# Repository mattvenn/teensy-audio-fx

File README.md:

# Teensy FX

* A [Teensy 4](https://www.pjrc.com/teensy-4-0/) based FX unit with [Pocket Operator](https://teenage.engineering/products/po) style and playability.
* 12 knobs, 4 buttons each with LED, and 4 LEDs showing automation cycle.
* Combination of filtered reverb, ping pong filtered delay and a noise source, but this is [customisable](#Audio-patch).
* Each knob can be automated (a bit like punch in effects on the Pocket Operators)
* Tap tempo and PO sync
* [video series on development and use of the teensy-fx](https://www.youtube.com/playlist?list=PLmcDgdDpcaPg4DthWWuq7HqhB-hiN_gUg)

# Hardware

[schematic](hardware/schematic.pdf)

[gerbers](hardware/teensy-fx-2020-02-10-fab.zip)

[photos](https://photos.app.goo.gl/ELiSmwA5KhBPN7PL9)

[noise performance](docs/noise.md)

Buy the right parts through the links on the [kitspace page](https://kitspace.org/boards/github.com/mattvenn/teensy-audio-fx).

## Hardware Resources

Based off the teensy 4 audio board and the [teensy beats shield](https://hackaday.io/project/161127-teensy-beats-shield)

* teensy 4 audio board schematic https://www.pjrc.com/store/schematic_audio4.png
* [SGTL5000 datasheet](https://static6.arrow.com/aropdfconversion/d5e3ddfdb01ac7d0ee29dd23626c23e0eb18a14a/1931605559406471sgtl5000.pdf)
* TLC5947 24 channel PWM LED driver
* 4067 multiplexer for the knobs
* pot RK09K1130AP5

## Hardware V1: git commit 99c1038

check the git repo out to the [hash](https://github.com/mattvenn/teensy-audio-fx/tree/99c1038) to make sure everything is in sync.

### Errata

* Do not place C16
* Swap LRCLK & BCLK - see pic [lrclk-bclk-swap](docs/lrclk-bclk-swap.png)
* 2.2uF ceramics sound as good and are much cheaper than the 1uF acrylics for C8, C9, C14 & C15

## Hardware V2: git master

* test points for mic input
* separate regulator for pot 3.3v to reduce noise?
* put leds and buttons below pots for easier viewing and pressing
* leave space on back for rubber feet
* update FP of audio sockets to new FP - audio sockets weren't available in EU, changed to 35RASMT2BHNTRX which has 5 pads but will fit on the same fp
* filter behind pot mux was a mistake. filters must be in front of mux or removed - fixed by removing
* fix LRCLK & BCLK mixup - fixed

## Back graphic

* Art by Kipling: http://bit.ly/39Wxc4R. Designed in ContextFree
* 100 x 60mm == 3.94 x 2.36" == 1182 x 708 pix

# FW

* each knob controls one of the parameters
* each knob has a number of steps of recordable automation
* knob's leds brightness shows current value of parameter
* record time is based on bpm tap tempo and number of steps (4 bars in control.py)
* buttons are: tap tempo/sync, write, erase and start automation loop from beginning
* press & hold tempo button to switch between tap tempo and [PO sync mode](docs/PO_sync_mode.md)
* press write and move a knob to record its movement
* moving a knob without pressing record will wipe the pattern and set it all to the current knob value
* 4 leds on top right show progression through the automation loop

## Uploading

* remove modemmanager
* install teensy rules: https://www.pjrc.com/teensy/00-teensy.rules

    sudo cp 49-teensy.rules /etc/udev/rules.d
    sudo udevadm control --reload-rules
    sudo udevadm trigger

Then:

    make prog

## issues

* freeverb [noise issue](https://forum.pjrc.com/threads/57046-Freeverb-with-low-input-levels-gt-noise-and-wierd-oscillating-quot-tone-quot) fixed [here](https://github.com/PaulStoffregen/Audio/pull/357)
    * to fix this you can copy the local effect_freeverb over the one in ~/.platformio
* if delay is not as long as expected (should be seconds), check teensy audio lib is up to date, older versions [didn't support teensy4's large memory](https://github.com/PaulStoffregen/Audio/commit/bbcfe3bd201d86aa7aa0e87d97c989f4259465de)

# Audio patch

made with https://www.pjrc.com/teensy/gui/index.html

# Software

[control.py](control.py) is a PyQT program that was developed in order to make an MVP
interface that could later be translated to hardware in the form of a PCB.

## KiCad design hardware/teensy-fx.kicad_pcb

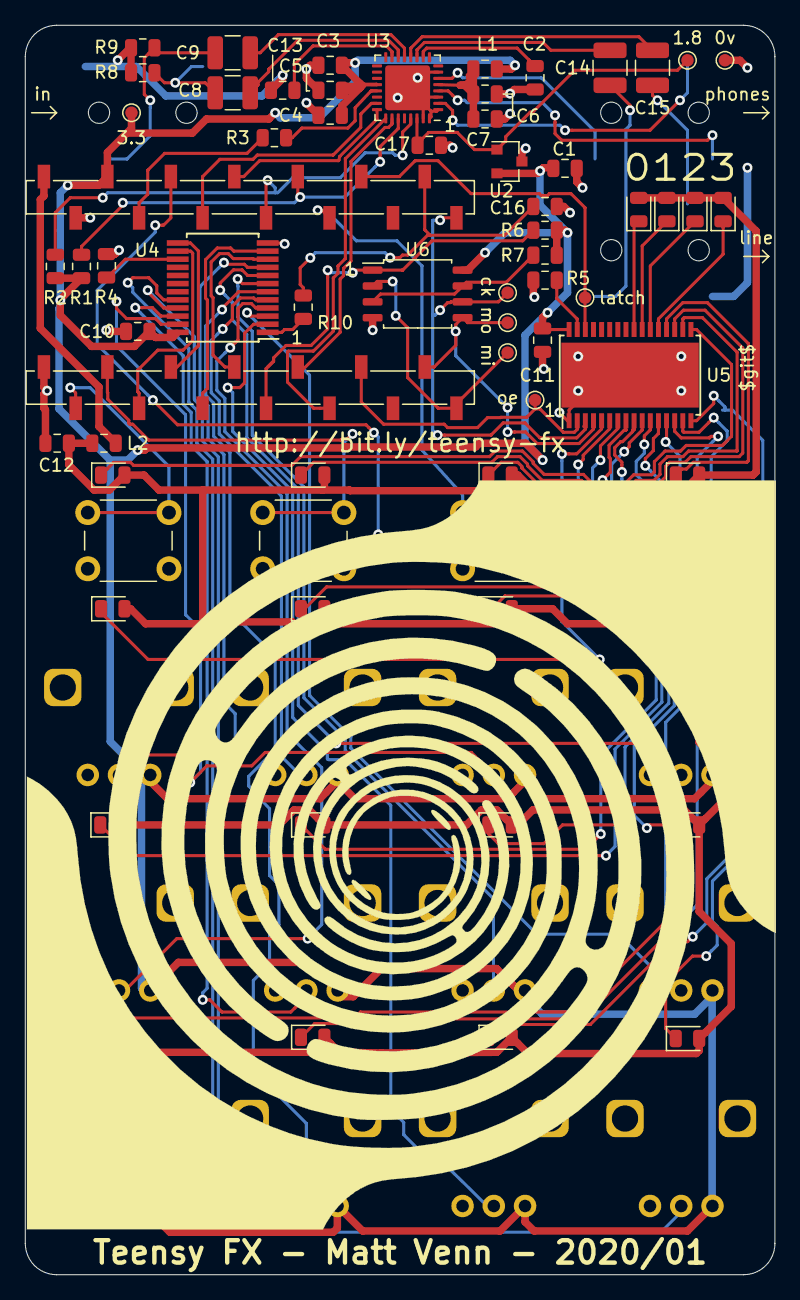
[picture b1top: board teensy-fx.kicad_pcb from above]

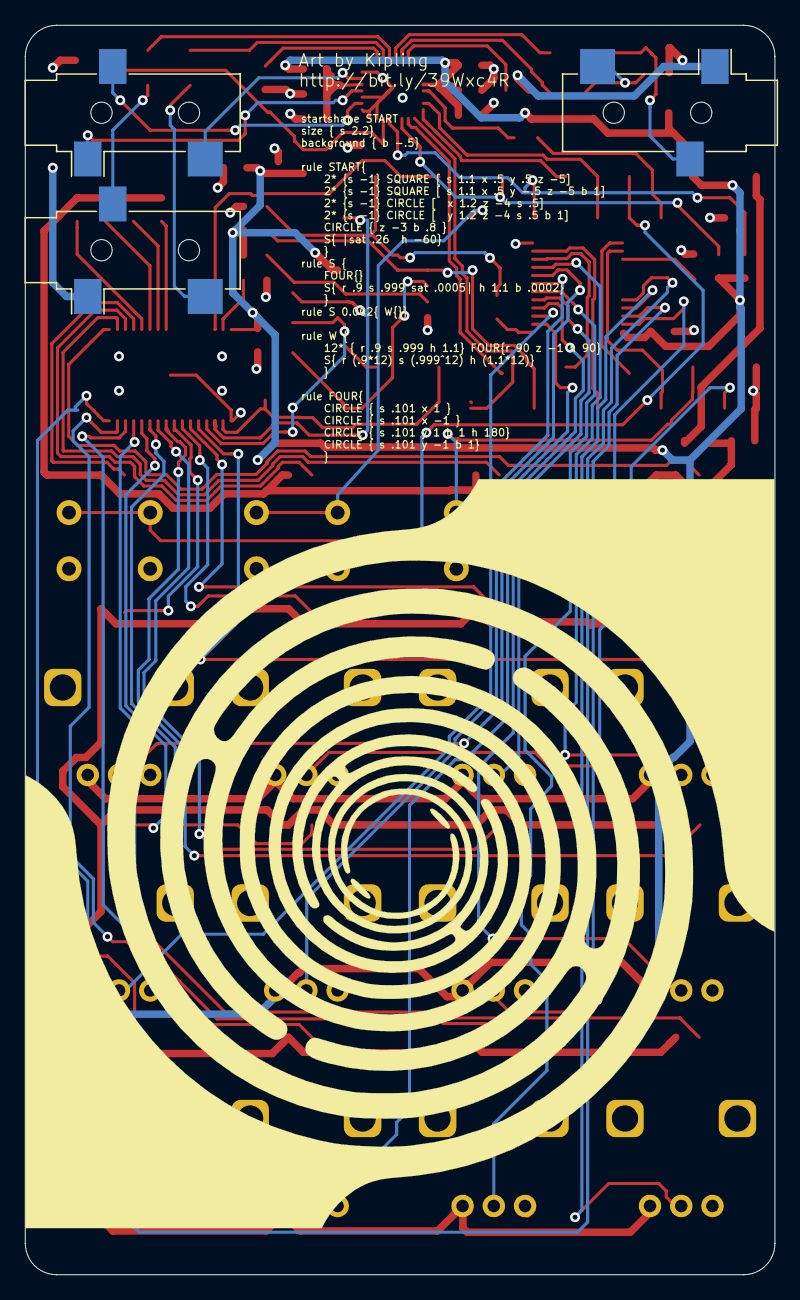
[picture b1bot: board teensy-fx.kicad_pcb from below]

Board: 4 copper layers, 60.0 x 100.0 mm, 82 parts (3 on the bottom side), 78 nets.

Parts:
C1, C3, C6, C10, C11, C12, C16, C17: 2.2uF; C_0805_2012Metric
C2, C4, C5, C7, C13: 0.1uF; C_0805_2012Metric
C8, C9, C14, C15: 1uF; C_1210_3225Metric
D1, D2, D3, D4, D5, D6, D7, D8, D9, D10, D11, D12, D13, D14, D15, D16, D17, D18, D19, D20: LED; LED_0805_2012Metric
J1, J2, J3: AudioJack3_Ground; Jack_3.5mm_CUI_SJ-3523-SMT_Horizontal
L1, L2: 600R; L_0805_2012Metric
R1, R2: 2.2K; R_0805_2012Metric
R3, R10: 100R; R_0805_2012Metric
R4, R6, R7: 10k; R_0805_2012Metric
R5: 4.7k; R_0805_2012Metric
R8, R9: 100k; R_0805_2012Metric
RV1, RV2, RV3, RV4, RV5, RV6, RV7, RV8, RV9, RV10, RV11, RV12: R_POT; Potentiometer_Alps_RK09L_Single_Vertical
SW1, SW2, SW3, SW4: Switch_SW_Push; SW_PUSH_6mm
TP1, TP2, TP3, TP4, TP5, TP6, TP7, TP8: TestPoint; TestPoint_Pad_D1.0mm
U1: Teensy4.0; teensy4smt
U2: MCP1811A; SOT-23
U3: SGTL5000; QFN-32-1EP_5x5mm_P0.5mm_EP3.6x3.6mm
U4: 4067; SSOP-24_5.3x8.2mm_P0.65mm
U5: TLC5947DAP; HTSSOP-32-1EP_6.1x11mm_P0.65mm_EP5.2x11mm_Mask4.11x4.36mm
U6: W25Q128JVS; SOIC-8_5.23x5.23mm_P1.27mm

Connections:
+1V8: C17.1, TP7.1, U2.1, U3.30
+3V3: C1.1, C3.1, C4.1, C5.1, C10.1, C11.1, L1.1, R1.1, R2.1, R6.1, R7.1, RV1.1, RV2.1, RV3.1, RV4.1, RV5.1, RV6.1, RV7.1, RV8.1, RV9.1, RV10.1, RV11.1, RV12.1, TP6.1, U1.31, U2.2, U3.20, U4.24, U5.32, U6.8
+5V: L2.1, U1.33
+5VA: C12.1, D1.2, D2.2, D3.2, D4.2, D5.2, D6.2, D7.2, D8.2, D9.2, D10.2, D11.2, D12.2, D13.2, D14.2, D15.2, D16.2, D17.2, D18.2, D19.2, D20.2, L2.2
/SGTL audio/filter_audio_3v3: C6.1, C7.1, L1.2, U3.5
/mem_cs: R6.2, U1.8, U6.1
/pots buttons & LEDs/a0: RV1.2, U4.9
/pots buttons & LEDs/a1: RV4.2, U4.8
/pots buttons & LEDs/a2: RV7.2, U4.7
/pots buttons & LEDs/a3: RV10.2, U4.6
/pots buttons & LEDs/a4: RV2.2, U4.5
/pots buttons & LEDs/a5: RV5.2, U4.4
/pots buttons & LEDs/a6: RV8.2, U4.3
/pots buttons & LEDs/a7: RV11.2, U4.2
/pots buttons & LEDs/a8: RV3.2, U4.23
/pots buttons & LEDs/a9: RV6.2, U4.22
/pots buttons & LEDs/a10: RV9.2, U4.21
/pots buttons & LEDs/a11: RV12.2, U4.20
BCLK: U1.28, U3.23
GND: C1.2, C2.2, C3.2, C4.2, C5.2, C6.2, C7.2, C10.2, C11.2, C12.2, C13.2, C16.2, C17.2, J1.S, J3.S, R4.2, R5.2, R8.2, R9.1, RV1.3, RV2.3, RV3.3, RV4.3, RV5.3, RV6.3, RV7.3, RV8.3, RV9.3, RV10.3, RV11.3, RV12.3, SW1.2, SW2.2, SW3.2, SW4.2, TP8.1, U1.1, U1.32, U2.3, U3.1, U3.3, U3.7, U3.31, U3.32, U3.33, U4.12, U5.1, U5.33, U6.4
I2S_IN: U1.10, U3.25
I2S_OUT: U1.9, U3.26
LRCLK: U1.27, U3.24
MCLK: R3.2, U1.30
MISO: TP5.1, U1.14, U6.2
MOSI: TP3.1, U1.13, U5.4, U6.5
unnamed: C2.1, U3.10
unnamed: C8.1, U3.14
unnamed: C8.2, J1.T, R8.1
unnamed: C9.1, U3.13
unnamed: C9.2, J1.R, R9.2
unnamed: C13.1, U3.15
unnamed: C14.1, U3.11
unnamed: C14.2, J3.T
unnamed: C15.1, U3.12
unnamed: C15.2, J3.R
unnamed: D1.1, U5.5
unnamed: D2.1, U5.6
unnamed: D3.1, U5.7
unnamed: D4.1, U5.8
unnamed: D5.1, U5.9
unnamed: D6.1, U5.10
unnamed: D7.1, U5.11
unnamed: D8.1, U5.12
unnamed: D9.1, U5.13
unnamed: D10.1, U5.14
unnamed: D11.1, U5.15
unnamed: D12.1, U5.16
unnamed: D13.1, U5.17
unnamed: D14.1, U5.18
unnamed: D15.1, U5.19
unnamed: D16.1, U5.20
unnamed: D17.1, U5.21
unnamed: D18.1, U5.22
unnamed: D19.1, U5.23
unnamed: D20.1, U5.24
unnamed: J2.R, U3.2
unnamed: J2.S, U3.4
unnamed: J2.T, U3.6
unnamed: R3.1, U3.21
unnamed: R4.1, U4.15
unnamed: R5.1, U5.31
unnamed: R7.2, U6.3, U6.7
unnamed: R10.1, U4.1
SCL: R2.2, U1.26, U3.29
SCLK: TP1.1, U1.20, U5.3, U6.6
SDA: R1.2, U1.25, U3.27
led_latch: TP4.1, U1.23, U5.30
led_oe: TP2.1, U1.11, U5.2
pot_b0: U1.7, U4.10
pot_b1: U1.6, U4.11
pot_b2: U1.4, U4.14
pot_b3: U1.5, U4.13
pot_multiplex: C16.1, R10.2, U1.21
sw_1: SW1.1, U1.2
sw_2: SW2.1, U1.3
sw_3: SW3.1, U1.24
sw_4: SW4.1, U1.29

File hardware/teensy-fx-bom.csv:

"Ref","Qnty","Value","Cmp name","Footprint","Description","Vendor","Vendor P/N","farnell #","MOQ","Lead Time"
"C1, C3, C6, C10, C11, C12, C16, C17, ","8","2.2uF","C_Small","Capacitor_SMD:C_0805_2012Metric","Unpolarized capacitor, small symbol","","","2773238","",""
"C2, C4, C5, C7, C13, ","5","0.1uF","C_Small","Capacitor_SMD:C_0805_2012Metric","Unpolarized capacitor, small symbol","","","1414663","",""
"C8, C9, C14, C15, ","4","1uF","C_Small","Capacitor_SMD:C_1210_3225Metric","Unpolarized capacitor, small symbol","","","2112915","",""
"D1, D2, D3, D4, D5, D6, D7, D8, D9, D10, D11, D12, D13, D14, D15, D16, D17, D18, D19, D20, ","20","LED","LED","LED_SMD:LED_0805_2012Metric","Light emitting diode","","","2099236","",""
"J1, J2, J3, ","3","AudioJack3_Ground","AudioJack3","audio-fx:Jack_3.5mm_CUI_SJ-3523-SMT_Horizontal","Audio Jack, 3 Poles (Stereo / TRS)","","","2915138","",""
"L1, L2, ","2","600R","Ferrite_Bead_Small","Inductor_SMD:L_0805_2012Metric","Ferrite bead, small symbol","","","2215655","",""
"R1, R2, ","2","2.2K","R","Resistor_SMD:R_0805_2012Metric","Resistor","","","1469887","",""
"R3, R10, ","2","100R","R","Resistor_SMD:R_0805_2012Metric","Resistor","","","1469862","",""
"R4, R6, R7, ","3","10k","R","Resistor_SMD:R_0805_2012Metric","Resistor","","","2906645","",""
"R5, ","1","4.7k","R","Resistor_SMD:R_0805_2012Metric","Resistor","","","1469923","",""
"R8, R9, ","2","100k","R","Resistor_SMD:R_0805_2012Metric","Resistor","","","1469860","",""
"RV1, RV2, RV3, RV4, RV5, RV6, RV7, RV8, RV9, RV10, RV11, RV12, ","12","R_POT","R_POT","audio-fx:Potentiometer_Alps_RK09L_Single_Vertical","Potentiometer","","","","",""
"SW1, SW2, SW3, SW4, ","4","Switch_SW_Push","Switch_SW_Push-teensy_beats-cache","Button_Switch_THT:SW_PUSH_6mm","","","","dnp","",""
"TP1, TP2, TP3, TP4, TP5, TP6, TP7, TP8, ","8","TestPoint","TestPoint","TestPoint:TestPoint_Pad_D1.0mm","test point","","","dnp","",""
"U1, ","1","Teensy4.0","Teensy4.0","audio-fx:teensy4smt","","","","2847911","",""
"U2, ","1","MCP1811A","ldo","Package_TO_SOT_SMD:SOT-23","","","","2990195","",""
"U3, ","1","SGTL5000","SparkFun-IC-Analog_SGTL5000-teensy_beats-cache","Package_DFN_QFN:QFN-32-1EP_5x5mm_P0.5mm_EP3.6x3.6mm","","","","2308049","",""
"U4, ","1","4067","4067-teensy_beats-cache","Package_SO:SSOP-24_5.3x8.2mm_P0.65mm","","","","3124957","",""
"U5, ","1","TLC5947DAP","TLC5947DAP","Package_SO:HTSSOP-32-1EP_6.1x11mm_P0.65mm_EP5.2x11mm_Mask4.11x4.36mm","24-Channel, 12-Bit PWM LED Driver, HTSSOP","","","1755259","",""
"U6, ","1","W25Q128JVS","W25Q128JVS","Package_SO:SOIC-8_5.23x5.23mm_P1.27mm","128Mb Serial Flash Memory, Standard/Dual/Quad SPI, SOIC-8","","","dnp","",""

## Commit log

2019-12-27 first draft fx unit
2019-12-27 serial control of params
2019-12-27 working ui
2019-12-27 sliders instead of knobs
2019-12-29 mix pre delay and bpf
2019-12-29 automation working
2019-12-29 periodically request audio and mem max
2019-12-29 reset seq button
2019-12-29 debug logging
2019-12-31 mix rev in instead of rev out, start looking at saving settings
2020-01-02 bug fix on freq/res mixup, route noise direct to op, ping pong delay, half freq, save and load vals/seqs
2020-01-02 high pas reverb input to avoid saturation
2020-01-02 first commit on pcb schematic
2020-01-02 initial schematic and parts layout
2020-01-02 start adding links
2020-01-03 switch to pwm led driver, first pass routing
2020-01-03 tidy schematic and finish layout
2020-01-03 made better fp for smt teensy, fixed some wiring errors
2020-01-03 added basic board control stuff to check for pin collisions
2020-01-03 missing files
2020-01-03 try to fix the wiring a bit, signal integrity might be an issue with 2 layer and teensy breakout
2020-01-03 more leds
2020-01-03 move to 4 layer board, change size for cost, add optional flash
2020-01-03 readme
2020-01-03 moved sockets in 2mm
2020-01-03 fix noise filter bug
2020-01-03 notes on parts
2020-01-03 add gui screenshot
2020-01-03 mock serial
2020-01-03 fix pic link
2020-01-03 remove not very useful crossfade params and neaten things up a bit
2020-01-04 fix sgtl5000 symbol error, add filter resistor and cap for unused mic input
2020-01-04 new layout following feedback from pjrc forum
2020-01-04 split power plane into 2
2020-01-05 changed 3v3 to gnd plane under audio circuitry, added lineout jack
2020-01-05 try adding resistors to all the i2s lines
2020-01-06 change 3v3 plane to gnd, route all i2s signals on top plane, add rc filter for ADC pot input
2020-01-08 notes, check current, add extra decoupling cap for reg, move led supply to 5v
2020-01-11 fix teensy smt fp for molex part
2020-01-11 footprints
2020-01-11 ready to order
2020-01-11 slightly improve ground layer by moving vias
2020-01-11 go back to circle holes after seeing gerbers exported ovals as offset circles
2020-01-11 add model number
2020-01-11 added gerbers and config
2020-01-11 board and schematic updated
2020-01-11 added link to gerbers
2020-01-11 changed to LDO that I can source from farnell
2020-01-11 new LDO
2020-01-11 date format change
2020-01-11 new gerbz
2020-01-11 farnell numbers
2020-01-12 change farnell field to farnell #
2020-01-12 fix library mess and get bom exported
2020-01-12 stereo noise
2020-01-12 missing silk graphics!
2020-01-12 cheaper caps and non-us 10k resistor
2020-01-14 fixed pullups, tested all ins and outs with scope while running
2020-01-17 wasn't keeping time, tried lower res and seems better
2020-01-17 serial port argument
2020-01-19 bpm detect from PO sync pulse
2020-02-03 start on OO firmware for board
2020-02-03 add farnell number for switches
2020-02-04 added bar timer, tests and fix up fx.ino
2020-02-04 little cleanup
2020-02-05 testing automation in hw
2020-02-06 try fix the automation part
2020-02-07 tests
2020-02-07 automation tested and working better
2020-02-08 leds working on board, need to fix pots multiplex address, audio i2s lines arent working
2020-02-09 worked out why pot mux was weird, add erase button
2020-02-09 fix lrclk and bclk on schematic and readme notes
2020-02-09 leds for bar timer
2020-02-09 gamma
2020-02-09 tweak change detect
2020-02-09 led bar timer
2020-02-10 updates for extra control arg and sub millisecond bar timer
2020-02-10 fractional millisecond handling for better timing accuracy
2020-02-10 increase to 512 steps
2020-02-10 remove blanking except at init, and limit max led to 1023
2020-02-10 pot mapping for correct order
2020-02-10 new control order, fix led max for bar and button leds, start bar timer after init light fade
2020-02-10 fix wiring & routing for lrclk and bclk, and removed lp filter behind pot mux
2020-02-10 new schematic and gerber export
2020-02-10 notes on delays
2020-02-12 notes on hwv2
2020-02-12 format
2020-02-12 flip board upside down for easier button/led viewing, increase output vol
2020-02-12 remove unnecessary setup
2020-02-14 add kitspace.yaml
2020-02-14 add link to kitspace page to readme
2020-02-15 notes on v2 hw
2020-02-15 tap tempo
2020-02-15 ignore and tidy
2020-02-15 ignore
2020-02-15 working sync and tap
2020-02-15 fix automation from the sync signal
2020-02-15 simplify and improve sync, add leds feedback for buttons
2020-02-15 remove serial prints
2020-02-17 assembled 2nd board and discovered 1st board has blanking problem that led to led issues. increased MAX_LED to 4095 and got rid of erroneous LED_MAX
2020-02-17 readme notes
2020-02-17 image of wiring lrclk and bclk swap
2020-02-18 link to po and google photos album
2020-02-18 add video link
2020-02-18 edit intro
2020-02-18 teensy link
2020-02-21 noise and sync mode
2020-02-21 fix links
2020-02-21 pulse details
2020-03-07 git info
2020-03-07 fix hash
2020-03-28 add a binary
2020-07-11 note on fixing freeverb noise
2020-07-12 notes on reverb and delay
2020-07-12 binary with fixed delay time and lower noise reverb
2020-11-27 route noies through delay and start in sync mode
2020-11-27 divide by 2 seems to take too long for the loop
2020-11-29 add binary
2021-05-02 upload instructions
2021-05-02 reduce noise level
2021-05-02 beat based delays
2021-05-02 added binary and releas enotes
2021-05-02 note on noise
2021-05-03 add makefile because Im bored of forgetting the pio options
2021-05-03 average beat_ms to get rid of jitter on the delay causing unwanted artifacts due to delay times changing
2021-05-03 slightly increase max noise amount
2021-05-03 keep track of freeverb
2021-05-03 new binary and updated readme
2021-09-18 update with Erics modded Reverb
